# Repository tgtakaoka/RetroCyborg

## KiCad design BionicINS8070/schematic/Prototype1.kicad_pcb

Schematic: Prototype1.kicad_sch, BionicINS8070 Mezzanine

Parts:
C1: 0.1u; C_Disc_D3.4mm_W2.1mm_P2.50mm
J1: BionicConnector; DIP-48_W7.62mm
U1: INS8070; DIP-40_W15.24mm
U2: 74HCT126; DIP-14_W7.62mm

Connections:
/P10: J1.2 (P10), U1.33 (D0)
/P11: J1.3 (P11), U1.32 (D1)
/P12: J1.4 (P12), U1.31 (D2)
/P13: J1.5 (P13), U1.30 (D3)
/P14: J1.6 (P14), U1.29 (D4)
/P15: J1.7 (P15), U1.28 (D5)
/P16: J1.8 (P16), U1.27 (D6)
/P17: J1.9 (P17), U1.26 (D7)
/P20: J1.47 (P20), U1.25 (A0)
/P21: J1.46 (P21), U1.24 (A1)
/P22: J1.45 (P22), U1.23 (A2)
/P23: J1.44 (P23), U1.22 (A3)
/P24: J1.43 (P24), U1.21 (A4)
/P25: J1.42 (P25), U1.19 (A5)
/P26: J1.41 (P26), U1.18 (A6)
/P27: J1.40 (P27), U1.17 (A7)
/P30: J1.11 (P30), U1.16 (A8)
/P31: J1.12 (P31), U1.15 (A9)
/P32: J1.13 (P32), U1.14 (A10)
/P33: J1.14 (P33), U1.13 (A11)
/P34: J1.15 (P34), U1.12 (A12)
/P35: J1.16 (P35), U1.11 (A13)
/P36: J1.17 (P36), U1.10 (A14)
/P37: J1.18 (P37), U1.9 (A15)
/P41: J1.37 (P41), U1.6 (~WDS)
/P42: J1.36 (P42), U1.39 (SB)
/P43: J1.35 (P43), U1.38 (SA)
/P44: J1.34 (P44), U1.34 (F1)
/P45: J1.33 (P45), U1.35 (F2)
/P46: J1.32 (P46), U2.2 (1A)
/P47: J1.31 (P47), U1.3 (~BREQ)
/P50: J1.20 (P50), U1.4 (~RDS)
/P51: J1.21 (P51), U1.36 (F3)
/P52: J1.22 (P52), U1.5 (~HOLD)
/P53: J1.23 (P53), U1.37 (~RST)
/P54: J1.29 (P54), U1.2 (~ENIN)
/P55: J1.28 (P55), U1.1 (~ENOUT)
GND: C1.2, J1.1 (GND), J1.48 (GND), U1.20 (GND), U2.4 (2OE), U2.5 (2A), U2.7 (GND), U2.9 (3A), U2.10 (3OE), U2.12 (4A), U2.13 (4OE)
unnamed: U1.8 (XIN), U2.3 (1Y)
VCC: C1.1, J1.24 (VCC), J1.25 (VCC), U1.40 (VCC), U2.1 (1OE), U2.14 (VCC)

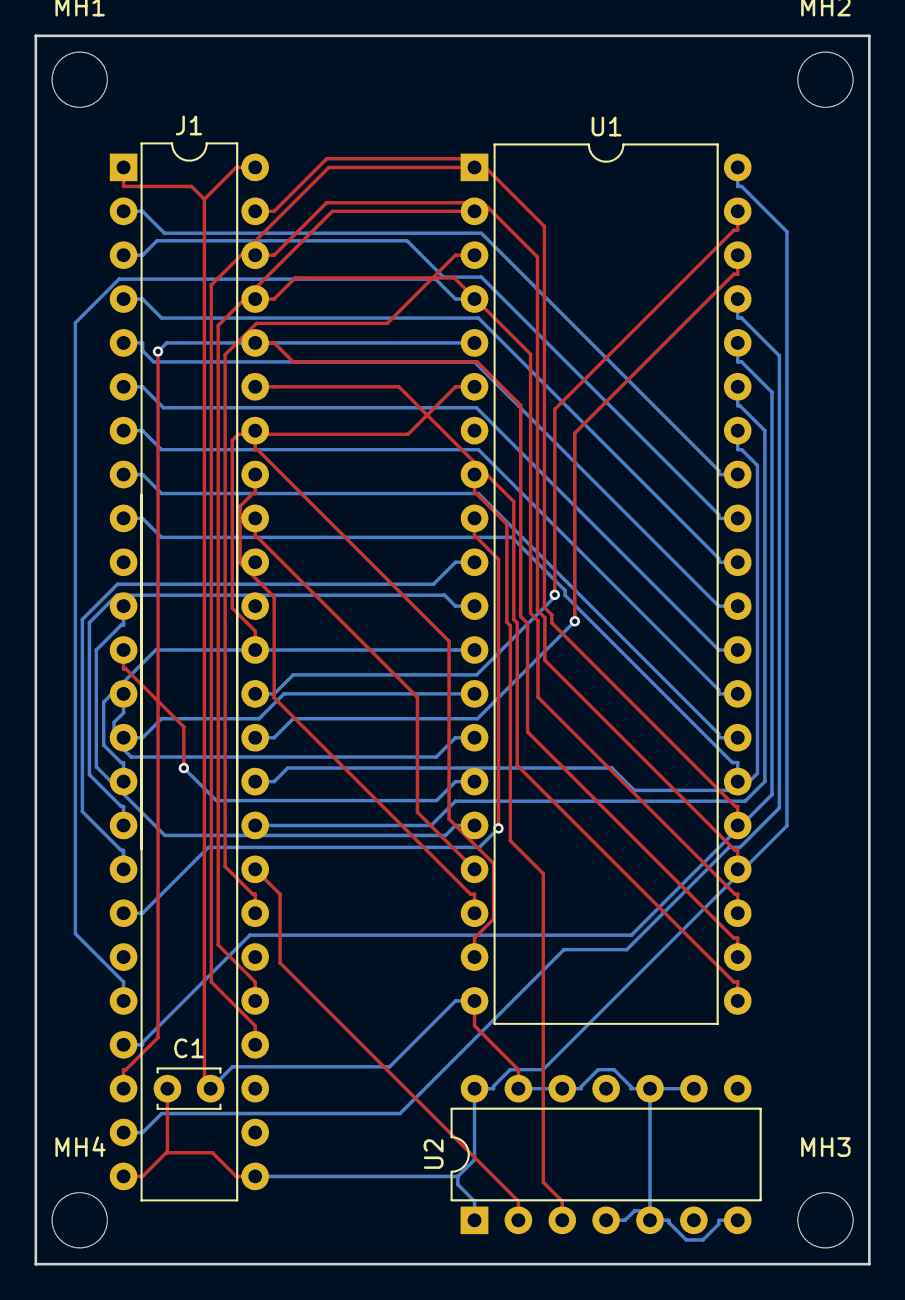
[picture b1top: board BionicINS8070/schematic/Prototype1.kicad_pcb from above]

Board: 2 copper layers, 48.3 x 71.1 mm, 8 parts (0 on the bottom side), 40 nets.

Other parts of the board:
MH1, MH2, MH3, MH4: MountingHole_3.2mm_M3

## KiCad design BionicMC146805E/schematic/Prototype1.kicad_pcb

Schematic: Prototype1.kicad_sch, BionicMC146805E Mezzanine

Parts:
C1: 0.1u; C_Disc_D3.4mm_W2.1mm_P2.50mm
J1: BionicConnector; DIP-48_W7.62mm
U1: MC146805E2P; DIP-40_W15.24mm
U2: 74HCT126; DIP-14_W7.62mm

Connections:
/P10: J1.2 (P10), U1.28 (B0)
/P11: J1.3 (P11), U1.27 (B1)
/P12: J1.4 (P12), U1.26 (B2)
/P13: J1.5 (P13), U1.25 (B3)
/P14: J1.6 (P14), U1.24 (B4)
/P15: J1.7 (P15), U1.23 (B5)
/P16: J1.8 (P16), U1.22 (B6)
/P17: J1.9 (P17), U1.21 (B7)
/P20: J1.47 (P20), U1.19 (A8)
/P21: J1.46 (P21), U1.18 (A9)
/P22: J1.45 (P22), U1.17 (A10)
/P23: J1.44 (P23), U1.16 (A11)
/P24: J1.43 (P24), U1.15 (A12)
/P40: J1.38 (P40), U1.6 (AS)
/P41: J1.37 (P41), U1.5 (R/~W)
/P42: J1.36 (P42), U2.9 (3A)
/P45: J1.33 (P45), U2.2 (1A)
/P46: J1.32 (P46), U2.5 (2A)
/P50: J1.20 (P50), U1.4 (DS)
/P51: J1.21 (P51), U1.3 (LI)
/P53: J1.23 (P53), U2.12 (4A)
GND: C1.2, J1.1 (GND), J1.48 (GND), U1.20 (VSS), U2.7 (GND)
unnamed: U1.1 (~RESET), U2.11 (4Y)
unnamed: U1.2 (~IRQ), U2.8 (3Y)
unnamed: U1.37 (TIMER), U2.3 (1Y)
unnamed: U1.39 (OSC1), U2.6 (2Y)
VCC: C1.1, J1.24 (VCC), J1.25 (VCC), U1.40 (VDD), U2.1 (1OE), U2.4 (2OE), U2.10 (3OE), U2.13 (4OE), U2.14 (VCC)

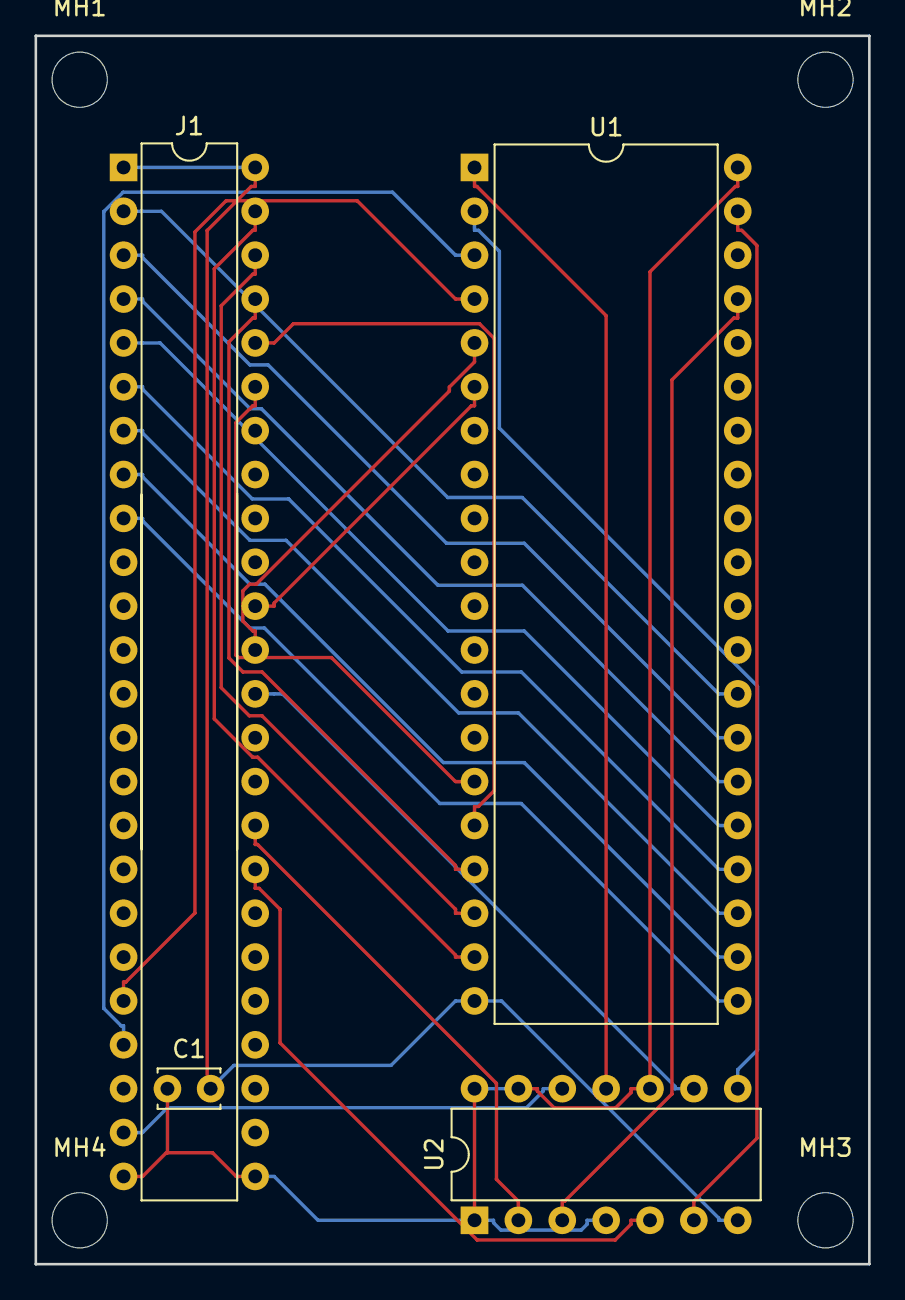
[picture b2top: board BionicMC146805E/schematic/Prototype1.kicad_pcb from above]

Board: 2 copper layers, 48.3 x 71.1 mm, 8 parts (0 on the bottom side), 27 nets.

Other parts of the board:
MH1, MH2, MH3, MH4: MountingHole_3.2mm_M3

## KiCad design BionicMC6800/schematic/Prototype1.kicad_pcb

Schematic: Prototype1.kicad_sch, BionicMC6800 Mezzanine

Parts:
C1: 0.1u; C_Disc_D3.4mm_W2.1mm_P2.50mm
J1: BionicConnector; DIP-48_W7.62mm
U1: MC6800P; DIP-40_W15.24mm
U2: 74HCT126; DIP-14_W7.62mm

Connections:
/P10: J1.2 (P10), U1.33 (D0)
/P11: J1.3 (P11), U1.32 (D1)
/P12: J1.4 (P12), U1.31 (D2)
/P13: J1.5 (P13), U1.30 (D3)
/P14: J1.6 (P14), U1.29 (D4)
/P15: J1.7 (P15), U1.28 (D5)
/P16: J1.8 (P16), U1.27 (D6)
/P17: J1.9 (P17), U1.26 (D7)
/P20: J1.47 (P20), U1.9 (A0)
/P21: J1.46 (P21), U1.10 (A1)
/P22: J1.45 (P22), U1.11 (A2)
/P23: J1.44 (P23), U1.12 (A3)
/P24: J1.43 (P24), U1.13 (A4)
/P25: J1.42 (P25), U1.14 (A5)
/P26: J1.41 (P26), U1.15 (A6)
/P27: J1.40 (P27), U1.16 (A7)
/P30: J1.11 (P30), U1.17 (A8)
/P31: J1.12 (P31), U1.18 (A9)
/P32: J1.13 (P32), U1.19 (A10)
/P33: J1.14 (P33), U1.20 (A11)
/P34: J1.15 (P34), U1.22 (A12)
/P35: J1.16 (P35), U1.23 (A13)
/P36: J1.17 (P36), U1.24 (A14)
/P37: J1.18 (P37), U1.25 (A15)
/P40: J1.38 (P40), U1.2 (~HALT)
/P41: J1.37 (P41), U1.34 (R/~W)
/P42: J1.36 (P42), U1.4 (~IRQ)
/P43: J1.35 (P43), U1.6 (~NMI)
/P46: J1.32 (P46), U2.2 (1A)
/P47: J1.31 (P47), U2.5 (2A)
/P50: J1.20 (P50), U1.5 (VMA)
/P52: J1.22 (P52), U1.36 (DBE)
/P53: J1.23 (P53), U1.40 (~RESET)
/P54: J1.29 (P54), U1.39 (TSC)
/P55: J1.28 (P55), U1.7 (BA)
GND: C1.2, J1.1 (GND), J1.48 (GND), U1.1 (VSS), U1.21 (VSS), U2.7 (GND), U2.9 (3A), U2.10 (3OE), U2.12 (4A), U2.13 (4OE)
unnamed: U1.3 (PHI1), U2.3 (1Y)
unnamed: U1.37 (PHI2), U2.6 (2Y)
VCC: C1.1, J1.24 (VCC), J1.25 (VCC), U1.8 (VCC), U2.1 (1OE), U2.4 (2OE), U2.14 (VCC)

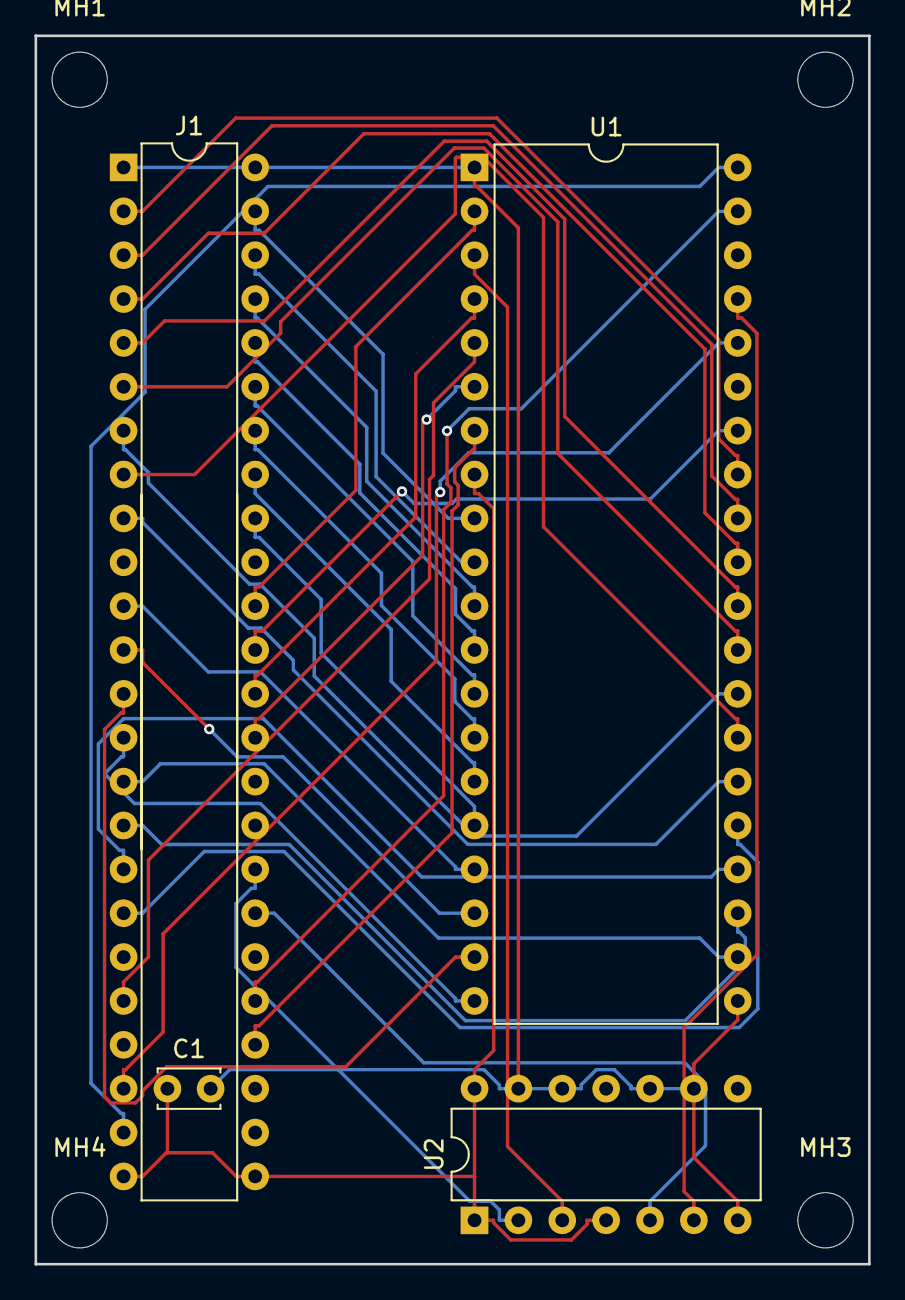
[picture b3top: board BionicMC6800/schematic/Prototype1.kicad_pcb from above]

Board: 2 copper layers, 48.3 x 71.1 mm, 8 parts (0 on the bottom side), 39 nets.

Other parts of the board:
MH1, MH2, MH3, MH4: MountingHole_3.2mm_M3

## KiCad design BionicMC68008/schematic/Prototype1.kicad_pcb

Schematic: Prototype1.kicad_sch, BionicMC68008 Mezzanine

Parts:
C1, C2, C3, C4: 0.1u; C_Disc_D3.4mm_W2.1mm_P2.50mm
J1: BionicConnector; DIP-48_W7.62mm
U1: MC68008P; DIP-48_W15.24mm
U2: 74HCT126; DIP-14_W7.62mm
U3, U4: 74HCT541; DIP-20_W7.62mm

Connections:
/P10: J1.2 (P10), U1.27 (D0)
/P11: J1.3 (P11), U1.26 (D1)
/P12: J1.4 (P12), U1.25 (D2)
/P13: J1.5 (P13), U1.24 (D3)
/P14: J1.6 (P14), U1.23 (D4)
/P15: J1.7 (P15), U1.22 (D5)
/P16: J1.8 (P16), U1.21 (D6)
/P17: J1.9 (P17), U1.20 (D7)
/P20: J1.47 (P20), U1.46 (A0)
/P21: J1.46 (P21), U1.47 (A1)
/P22: J1.45 (P22), U1.48 (A2)
/P23: J1.44 (P23), U1.1 (A3)
/P24: J1.43 (P24), U1.2 (A4)
/P25: J1.42 (P25), U1.3 (A5)
/P26: J1.41 (P26), U1.4 (A6)
/P27: J1.40 (P27), U1.5 (A7)
/P30: J1.11 (P30), U3.18 (Y0), U4.18 (Y0)
/P31: J1.12 (P31), U3.17 (Y1), U4.17 (Y1)
/P32: J1.13 (P32), U3.16 (Y2), U4.16 (Y2)
/P33: J1.14 (P33), U3.15 (Y3), U4.15 (Y3)
/P34: J1.15 (P34), U3.14 (Y4), U4.14 (Y4)
/P35: J1.16 (P35), U3.13 (Y5), U4.13 (Y5)
/P36: J1.17 (P36), U3.12 (Y6), U4.12 (Y6)
/P37: J1.18 (P37), U4.11 (Y7)
/P40: J1.38 (P40), U1.28 (~AS)
/P41: J1.37 (P41), U1.30 (R/~W)
/P42: J1.36 (P42), U1.42 (~IPL20)
/P43: J1.35 (P43), U1.41 (~IPL1)
/P44: J1.34 (P44), U1.32 (~BG)
/P45: J1.33 (P45), U1.40 (~BERR)
/P46: J1.32 (P46), U2.2 (1A)
/P47: J1.31 (P47), U1.33 (~BR)
/P50: J1.20 (P50), U1.29 (~DS)
/P51: J1.21 (P51), U1.36 (~HALT)
/P52: J1.22 (P52), U1.31 (~DTACK)
/P53: J1.23 (P53), U1.37 (~RESET)
/P54: J1.29 (P54), U4.1 (G1), U4.19 (G2)
/P55: J1.28 (P55), U3.1 (G1), U3.19 (G2)
GND: C1.2, C2.2, C3.2, C4.2, J1.1 (GND), J1.48 (GND), U1.15 (GND), U1.35 (GND), U2.4 (2OE), U2.5 (2A), U2.7 (GND), U2.9 (3A), U2.10 (3OE), U2.12 (4A), U2.13 (4OE), U3.9 (A7), U3.10 (GND), U4.10 (GND)
unnamed: U1.6 (A8), U4.2 (A0)
unnamed: U1.7 (A9), U4.3 (A1)
unnamed: U1.8 (A10), U4.4 (A2)
unnamed: U1.9 (A11), U4.5 (A3)
unnamed: U1.10 (A12), U4.6 (A4)
unnamed: U1.11 (A13), U4.7 (A5)
unnamed: U1.12 (A14), U4.8 (A6)
unnamed: U1.14 (A15), U4.9 (A7)
unnamed: U1.16 (A16), U3.2 (A0)
unnamed: U1.17 (A17), U3.3 (A1)
unnamed: U1.18 (A18), U3.4 (A2)
unnamed: U1.19 (A19), U3.5 (A3)
unnamed: U1.34 (CLK), U2.3 (1Y)
unnamed: U1.43 (FC2), U3.8 (A6)
unnamed: U1.44 (FC1), U3.7 (A5)
unnamed: U1.45 (FC0), U3.6 (A4)
VCC: C1.1, C2.1, C3.1, C4.1, J1.24 (VCC), J1.25 (VCC), U1.13 (VCC), U2.1 (1OE), U2.14 (VCC), U3.20 (VCC), U4.20 (VCC)

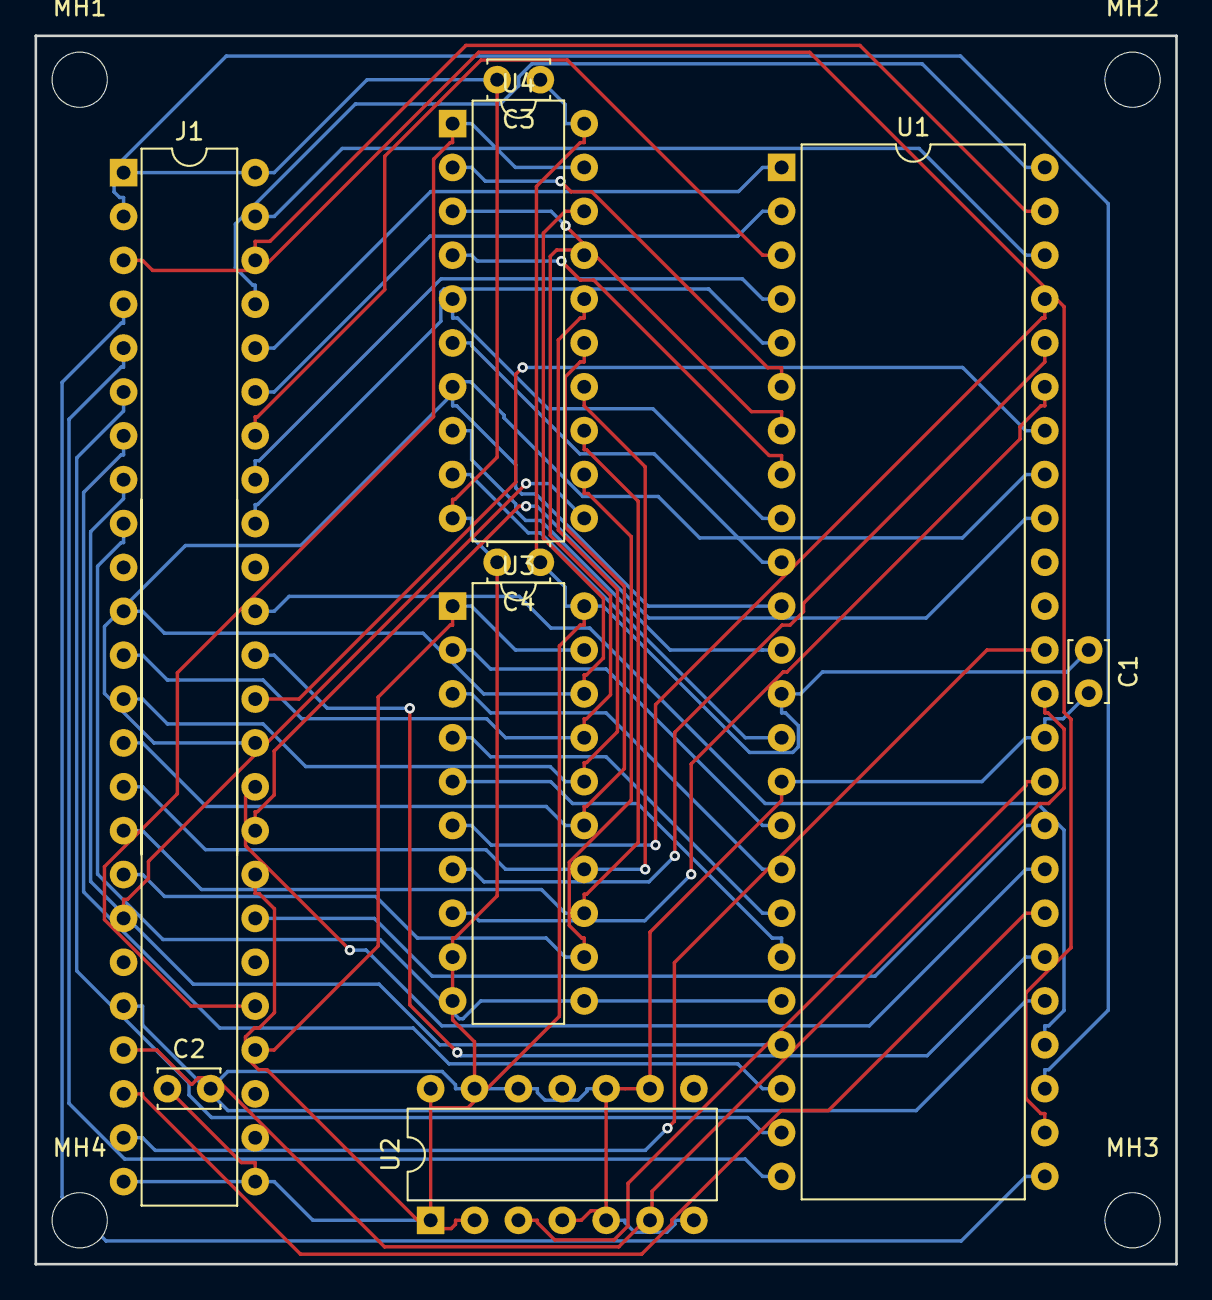
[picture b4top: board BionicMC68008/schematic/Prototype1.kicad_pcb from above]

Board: 2 copper layers, 66.0 x 71.1 mm, 13 parts (0 on the bottom side), 56 nets.

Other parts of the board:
MH1, MH2, MH3, MH4: MountingHole_3.2mm_M3

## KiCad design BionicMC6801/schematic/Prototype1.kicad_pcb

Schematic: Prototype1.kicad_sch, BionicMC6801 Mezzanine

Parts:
C1: 0.1u; C_Disc_D3.4mm_W2.1mm_P2.50mm
J1: BionicConnector; DIP-48_W7.62mm
JP1: MC/HD; PinHeader_1x03_P2.54mm_Vertical
JP2: SingleStep; PinHeader_1x03_P2.54mm_Vertical
U1: MC6801P; DIP-40_W15.24mm
U2: 74HCT126; DIP-14_W7.62mm

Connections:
/#RESET: U1.6 (~RESET), U2.3 (1Y)
/P10: J1.2 (P10), U1.37 (AD0)
/P11: J1.3 (P11), U1.36 (AD1)
/P12: J1.4 (P12), U1.35 (AD2)
/P13: J1.5 (P13), U1.34 (AD3)
/P14: J1.6 (P14), U1.33 (AD4)
/P15: J1.7 (P15), U1.32 (AD5)
/P16: J1.8 (P16), U1.31 (AD6)
/P17: J1.9 (P17), U1.30 (AD7)
/P20: J1.47 (P20), U1.29 (A8)
/P21: J1.46 (P21), U1.28 (A9)
/P22: J1.45 (P22), U1.27 (A10)
/P23: J1.44 (P23), U1.26 (A11)
/P24: J1.43 (P24), U1.25 (A12)
/P25: J1.42 (P25), U1.24 (A13)
/P26: J1.41 (P26), U1.23 (A14)
/P27: J1.40 (P27), U1.22 (A15)
/P30: J1.11 (P30), U1.13 (P10)
/P31: J1.12 (P31), U1.14 (P11)
/P32: J1.13 (P32), U1.15 (P12)
/P33: J1.14 (P33), U1.16 (P13)
/P34: J1.15 (P34), U1.17 (P14)
/P35: J1.16 (P35), U1.18 (P15)
/P36: J1.17 (P36), U1.19 (P16)
/P37: J1.18 (P37), U1.20 (P17)
/P40: J1.38 (P40), U1.39 (AS)
/P41: J1.37 (P41), U1.38 (R/~W)
/P42: J1.36 (P42), U1.5 (~IRQ1)
/P43: J1.35 (P43), JP2.2 (C), U1.4 (~NMI)
/P44: J1.34 (P44), U1.12 (TxD/P24)
/P45: J1.33 (P45), U1.11 (RxD/P23)
/P46: J1.32 (P46), U2.5 (2A)
/P47: J1.31 (P47), U1.40 (E)
/P50: J1.20 (P50), U1.8 (PC0/P20)
/P51: J1.21 (P51), U1.9 (PC1/P21)
/P52: J1.22 (P52), JP2.3 (B), U1.10 (PC2/P22)
/P53: J1.23 (P53), U2.2 (1A)
/P55: J1.28 (P55), JP1.2 (C), U1.2 (XTAL)
GND: C1.2, J1.1 (GND), J1.48 (GND), JP1.1 (A), U1.1 (VSS), U1.21 (VCCstandby), U2.7 (GND), U2.9 (3A), U2.10 (3OE), U2.12 (4A), U2.13 (4OE)
unnamed: U1.3 (EXTAL), U2.6 (2Y)
VCC: C1.1, J1.24 (VCC), J1.25 (VCC), U1.7 (VCC), U2.1 (1OE), U2.4 (2OE), U2.14 (VCC)

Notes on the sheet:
MODE2
For LILBUG

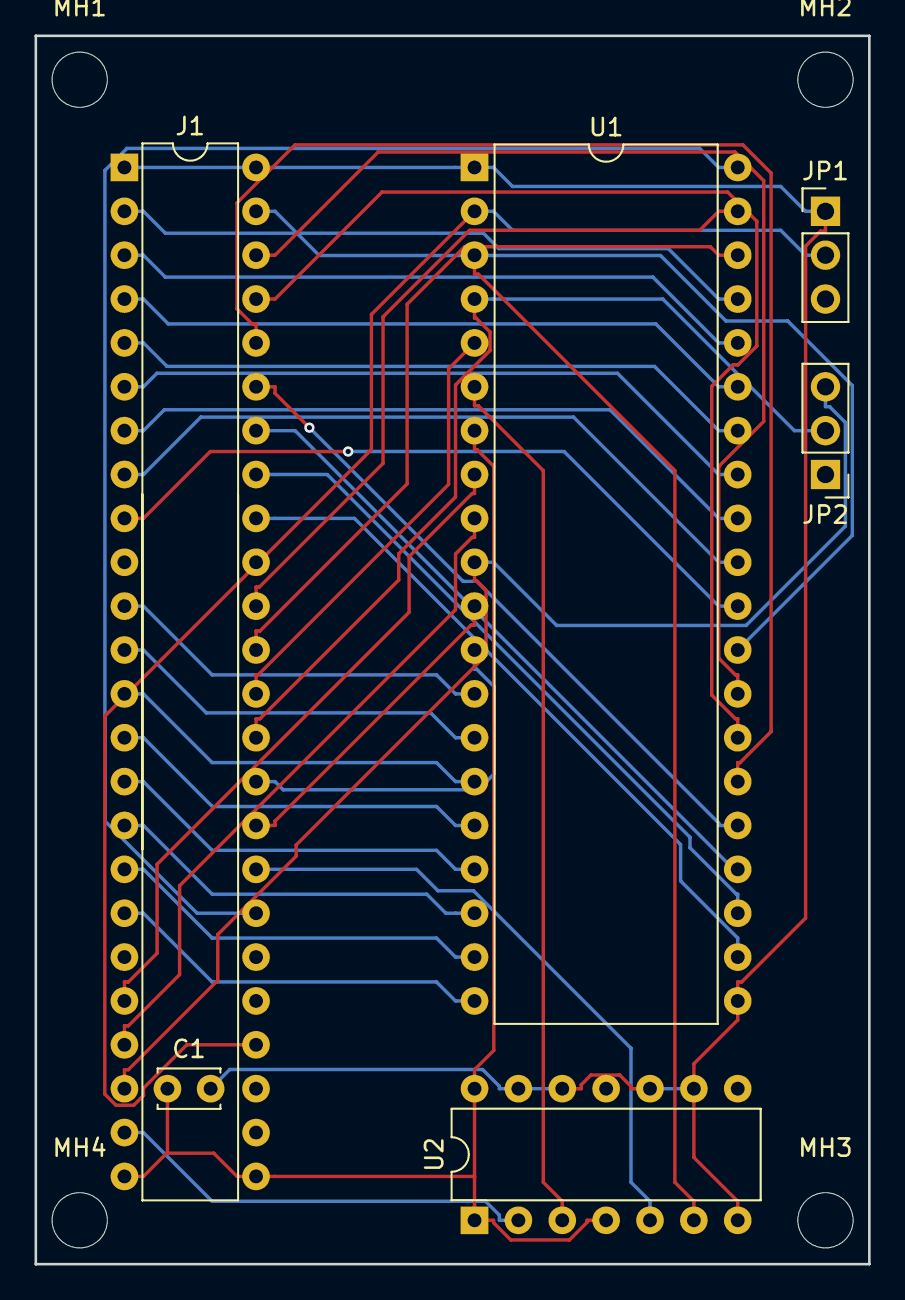
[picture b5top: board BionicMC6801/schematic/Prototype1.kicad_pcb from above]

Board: 2 copper layers, 48.3 x 71.1 mm, 10 parts (0 on the bottom side), 41 nets.

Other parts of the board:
MH1, MH2, MH3, MH4: MountingHole_3.2mm_M3

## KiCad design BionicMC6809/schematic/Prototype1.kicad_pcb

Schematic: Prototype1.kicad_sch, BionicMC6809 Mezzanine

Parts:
C1: 0.1u; C_Disc_D3.4mm_W2.1mm_P2.50mm
J1: BionicConnector; DIP-48_W7.62mm
JP1: HD63/MC68; PinHeader_1x03_P2.54mm_Vertical
U1: MC6809P; DIP-40_W15.24mm
U2: 74HCT126; DIP-14_W7.62mm

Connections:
/EXTAL: U1.38 (EXTAL), U2.6 (2Y)
/P10: J1.2 (P10), U1.31 (D0)
/P11: J1.3 (P11), U1.30 (D1)
/P12: J1.4 (P12), U1.29 (D2)
/P13: J1.5 (P13), U1.28 (D3)
/P14: J1.6 (P14), U1.27 (D4)
/P15: J1.7 (P15), U1.26 (D5)
/P16: J1.8 (P16), U1.25 (D6)
/P17: J1.9 (P17), U1.24 (D7)
/P20: J1.47 (P20), U1.8 (A0)
/P21: J1.46 (P21), U1.9 (A1)
/P22: J1.45 (P22), U1.10 (A2)
/P23: J1.44 (P23), U1.11 (A3)
/P24: J1.43 (P24), U1.12 (A4)
/P25: J1.42 (P25), U1.13 (A5)
/P26: J1.41 (P26), U1.14 (A6)
/P27: J1.40 (P27), U1.15 (A7)
/P30: J1.11 (P30), U1.16 (A8)
/P31: J1.12 (P31), U1.17 (A9)
/P32: J1.13 (P32), U1.18 (A10)
/P33: J1.14 (P33), U1.19 (A11)
/P34: J1.15 (P34), U1.20 (A12)
/P35: J1.16 (P35), U1.21 (A13)
/P36: J1.17 (P36), U1.22 (A14)
/P37: J1.18 (P37), U1.23 (A15)
/P40: J1.38 (P40), U1.40 (~HALT)
/P41: J1.37 (P41), U1.32 (R/~W)
/P42: J1.36 (P42), U1.3 (~IRQ)
/P43: J1.35 (P43), U1.2 (~NMI)
/P44: J1.34 (P44), U1.35 (Q)
/P45: J1.33 (P45), U1.4 (~FIRQ)
/P46: J1.32 (P46), U2.5 (2A)
/P47: J1.31 (P47), U1.34 (E)
/P50: J1.20 (P50), JP1.2 (C), U1.39 (XTAL)
/P51: J1.21 (P51), U1.5 (BS)
/P52: J1.22 (P52), U1.36 (MRDY)
/P53: J1.23 (P53), U2.2 (1A)
/P54: J1.29 (P54), U1.33 (~DMA/BREQ)
/P55: J1.28 (P55), U1.6 (BA)
GND: C1.2, J1.1 (GND), J1.48 (GND), JP1.1 (A), U1.1 (VSS), U2.7 (GND), U2.9 (3A), U2.10 (3OE), U2.12 (4A), U2.13 (4OE)
unnamed: U1.37 (~RESET), U2.3 (1Y)
VCC: C1.1, J1.24 (VCC), J1.25 (VCC), U1.7 (VCC), U2.1 (1OE), U2.4 (2OE), U2.14 (VCC)

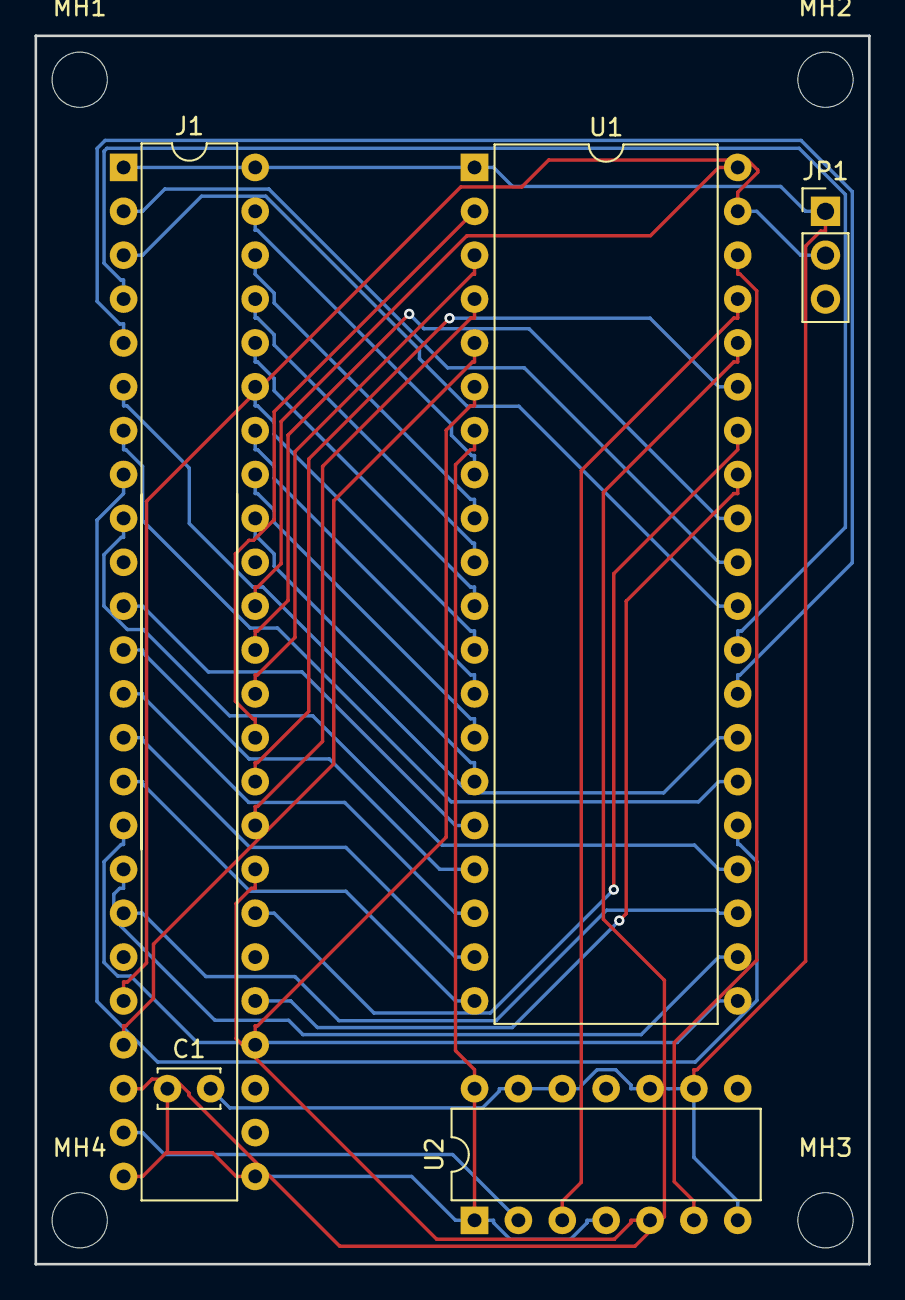
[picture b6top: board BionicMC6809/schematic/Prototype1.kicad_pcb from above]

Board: 2 copper layers, 48.3 x 71.1 mm, 9 parts (0 on the bottom side), 42 nets.

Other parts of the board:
MH1, MH2, MH3, MH4: MountingHole_3.2mm_M3
